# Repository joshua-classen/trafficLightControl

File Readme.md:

Traffic Light Control | Assembly

This is a school project in which I designed a traffic light circuit for the ATMega16. EAGLE files are included. The program was written in assembler.

I had uploaded this project to bitbucket years ago: https://bitbucket.org/ckrex/trafficlightcontrol/src/master/

The Code was written in Atmel AVR studio.

There is also a demo on youtube where I explain the Traffic Light Control:

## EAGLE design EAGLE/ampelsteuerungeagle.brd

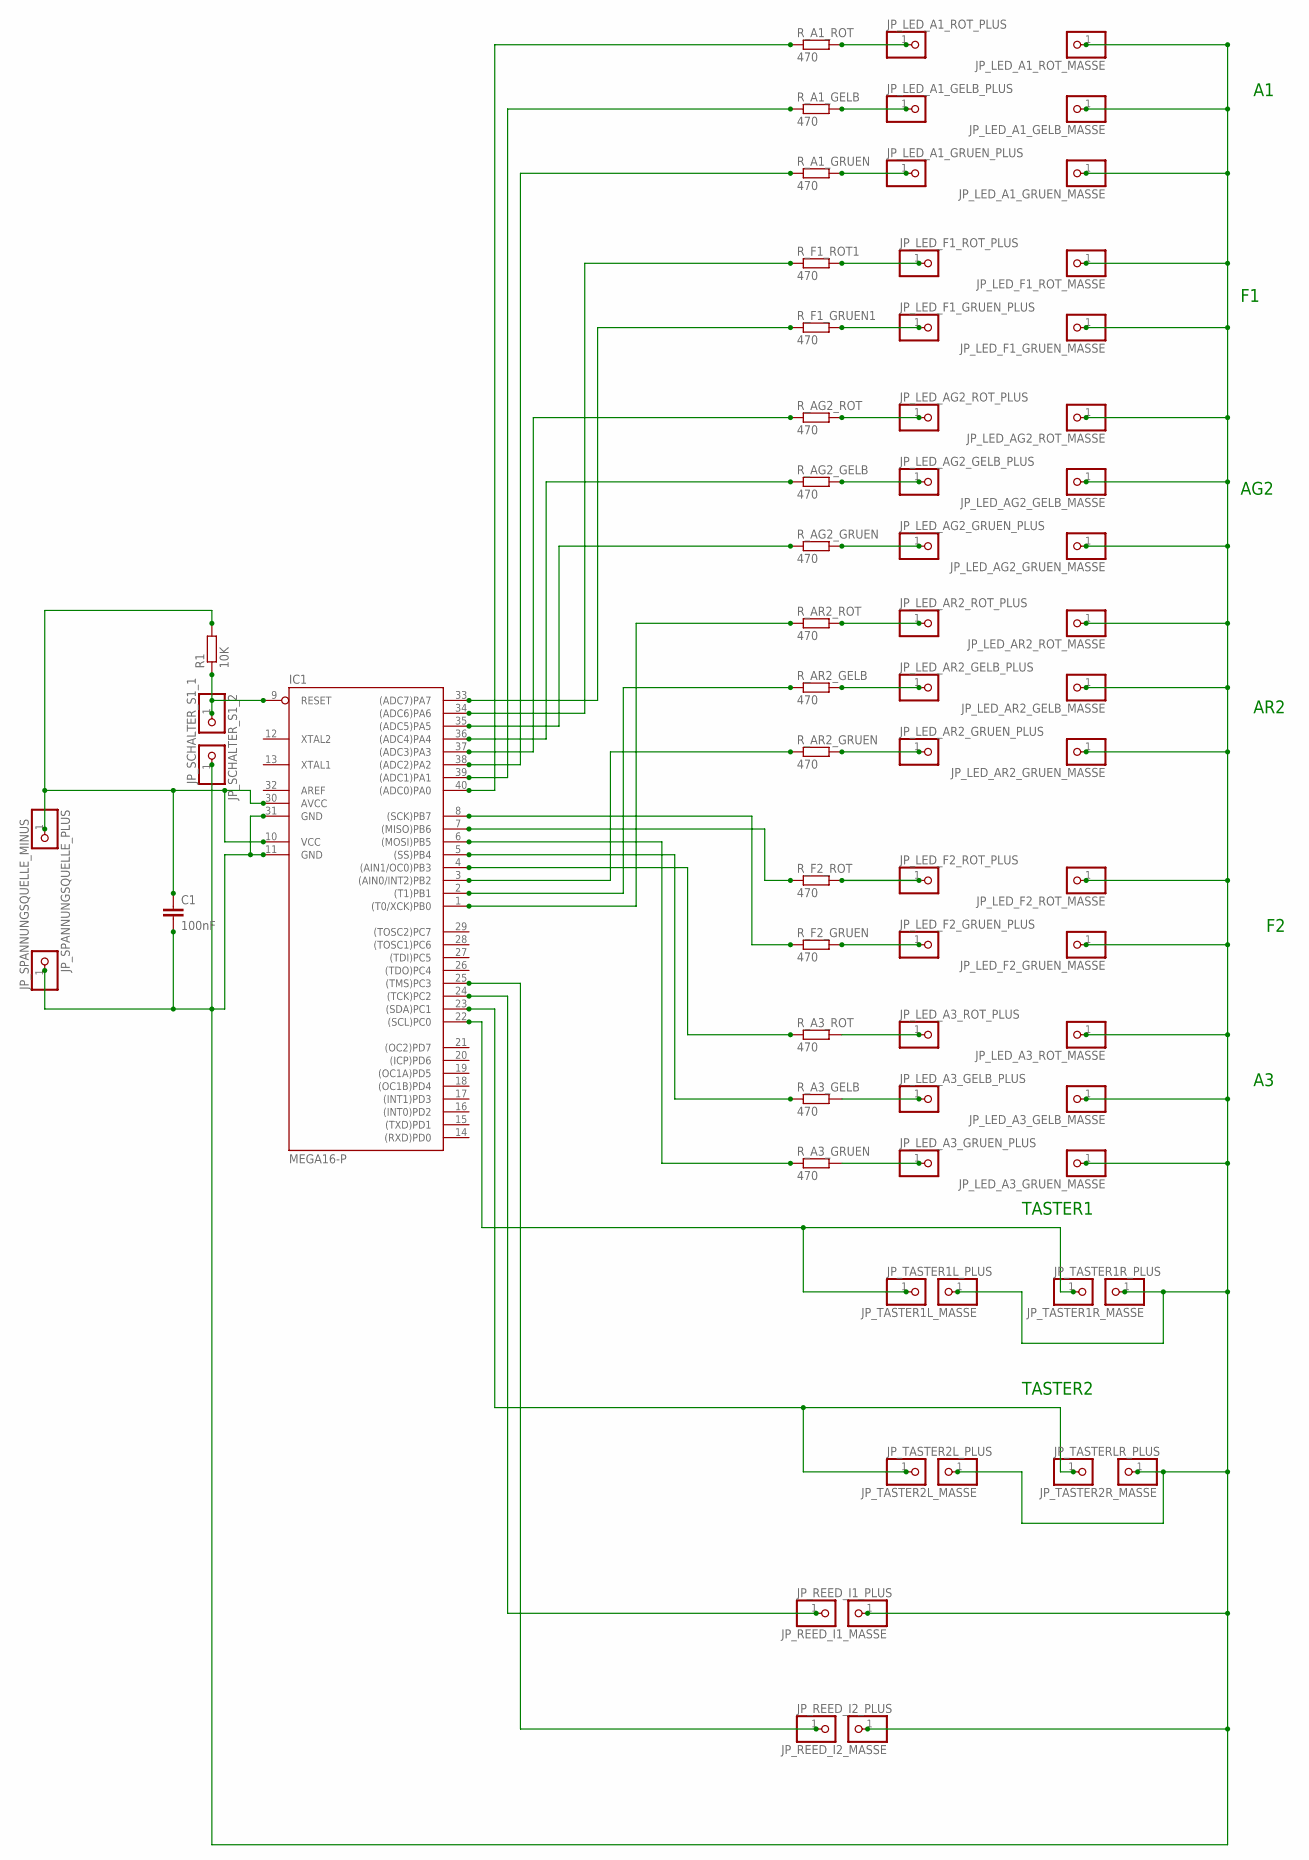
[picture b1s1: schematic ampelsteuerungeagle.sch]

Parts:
C1: 100nF; C025-024X044
IC1: MEGA16-P; DIL40
JP_LED_A1_GELB_MASSE, JP_LED_A1_GELB_PLUS, JP_LED_A1_GRUEN_MASSE, JP_LED_A1_GRUEN_PLUS, JP_LED_A1_ROT_MASSE, JP_LED_A1_ROT_PLUS, JP_LED_A3_GELB_MASSE, JP_LED_A3_GELB_PLUS, JP_LED_A3_GRUEN_MASSE, JP_LED_A3_GRUEN_PLUS, JP_LED_A3_ROT_MASSE, JP_LED_A3_ROT_PLUS: PINHD-1X1; 1X01
JP_LED_AG2_GELB_MASSE, JP_LED_AG2_GELB_PLUS, JP_LED_AG2_GRUEN_MASSE, JP_LED_AG2_GRUEN_PLUS, JP_LED_AG2_ROT_MASSE, JP_LED_AG2_ROT_PLUS: PINHD-1X1; 1X01
JP_LED_AR2_GELB_MASSE, JP_LED_AR2_GELB_PLUS, JP_LED_AR2_GRUEN_MASSE, JP_LED_AR2_GRUEN_PLUS, JP_LED_AR2_ROT_MASSE, JP_LED_AR2_ROT_PLUS: PINHD-1X1; 1X01
JP_LED_F1_GRUEN_MASSE, JP_LED_F1_GRUEN_PLUS, JP_LED_F1_ROT_MASSE, JP_LED_F1_ROT_PLUS, JP_LED_F2_GRUEN_MASSE, JP_LED_F2_GRUEN_PLUS, JP_LED_F2_ROT_MASSE, JP_LED_F2_ROT_PLUS: PINHD-1X1; 1X01
JP_REED_I1_MASSE, JP_REED_I1_PLUS, JP_REED_I2_MASSE, JP_REED_I2_PLUS: PINHD-1X1; 1X01
JP_SCHALTER_S1_1, JP_SCHALTER_S1_2: PINHD-1X1; 1X01
JP_SPANNUNGSQUELLE_MINUS: PINHD-1X1; 1X01
JP_SPANNUNGSQUELLE_PLUS: PINHD-1X1; 1X01
JP_TASTER1L_MASSE, JP_TASTER1L_PLUS, JP_TASTER1R_MASSE, JP_TASTER1R_PLUS, JP_TASTER2L_MASSE, JP_TASTER2L_PLUS, JP_TASTER2R_MASSE: PINHD-1X1; 1X01
JP_TASTERLR_PLUS: PINHD-1X1; 1X01
R1: 10K; 0204V
R_A1_GELB, R_A1_GRUEN, R_A1_ROT, R_A3_GELB, R_A3_GRUEN, R_A3_ROT: 470; 0204/7
R_AG2_GELB, R_AG2_GRUEN, R_AG2_ROT: 470; 0204/7
R_AR2_GELB, R_AR2_GRUEN, R_AR2_ROT: 470; 0204/7
R_F1_GRUEN1, R_F1_ROT1, R_F2_GRUEN, R_F2_ROT: 470; 0204/7

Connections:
unnamed: C1.1, IC1.10 (VCC), IC1.30 (AVCC), JP_SPANNUNGSQUELLE_PLUS.1, R1.2
unnamed: IC1.22 ((SCL)PC0), JP_TASTER1L_PLUS.1, JP_TASTER1R_PLUS.1
unnamed: IC1.40 ((ADC0)PA0), R_A1_ROT.1
unnamed: IC1.39 ((ADC1)PA1), R_A1_GELB.1
unnamed: IC1.38 ((ADC2)PA2), R_A1_GRUEN.1
unnamed: IC1.37 ((ADC3)PA3), R_AG2_ROT.1
unnamed: IC1.36 ((ADC4)PA4), R_AG2_GELB.1
unnamed: IC1.35 ((ADC5)PA5), R_AG2_GRUEN.1
unnamed: IC1.34 ((ADC6)PA6), R_F1_ROT1.1
unnamed: IC1.33 ((ADC7)PA7), R_F1_GRUEN1.1
unnamed: IC1.1 ((T0/XCK)PB0), R_AR2_ROT.1
unnamed: IC1.2 ((T1)PB1), R_AR2_GELB.1
unnamed: IC1.3 ((AIN0/INT2)PB2), R_AR2_GRUEN.1
unnamed: IC1.4 ((AIN1/OC0)PB3), R_A3_ROT.1
unnamed: IC1.5 ((SS)PB4), R_A3_GELB.1
unnamed: IC1.6 ((MOSI)PB5), R_A3_GRUEN.1
unnamed: IC1.7 ((MISO)PB6), R_F2_ROT.1
unnamed: JP_LED_AR2_GRUEN_PLUS.1, R_AR2_GRUEN.2
unnamed: JP_LED_A3_ROT_PLUS.1, R_A3_ROT.2
unnamed: JP_LED_AR2_GELB_PLUS.1, R_AR2_GELB.2
unnamed: JP_LED_AR2_ROT_PLUS.1, R_AR2_ROT.2
unnamed: JP_LED_AG2_GRUEN_PLUS.1, R_AG2_GRUEN.2
unnamed: JP_LED_AG2_GELB_PLUS.1, R_AG2_GELB.2
unnamed: JP_LED_AG2_ROT_PLUS.1, R_AG2_ROT.2
unnamed: JP_LED_A1_GRUEN_PLUS.1, R_A1_GRUEN.2
unnamed: JP_LED_A1_GELB_PLUS.1, R_A1_GELB.2
unnamed: JP_LED_A1_ROT_PLUS.1, R_A1_ROT.2
unnamed: JP_LED_F1_ROT_PLUS.1, R_F1_ROT1.2
unnamed: JP_LED_F1_GRUEN_PLUS.1, R_F1_GRUEN1.2
unnamed: JP_LED_F2_ROT_PLUS.1, R_F2_ROT.2
unnamed: JP_LED_F2_GRUEN_PLUS.1, R_F2_GRUEN.2
unnamed: JP_LED_A3_GELB_PLUS.1, R_A3_GELB.2
unnamed: JP_LED_A3_GRUEN_PLUS.1, R_A3_GRUEN.2
unnamed: IC1.9 (RESET), JP_SCHALTER_S1_2.1, R1.1
unnamed: IC1.23 ((SDA)PC1), JP_TASTER2L_PLUS.1, JP_TASTERLR_PLUS.1
unnamed: IC1.24 ((TCK)PC2), JP_REED_I1_PLUS.1
unnamed: C1.2, IC1.11 (GND), IC1.31 (GND), JP_LED_A1_GELB_MASSE.1, JP_LED_A1_GRUEN_MASSE.1, JP_LED_A1_ROT_MASSE.1, JP_LED_A3_GELB_MASSE.1, JP_LED_A3_GRUEN_MASSE.1, JP_LED_A3_ROT_MASSE.1, JP_LED_AG2_GELB_MASSE.1, JP_LED_AG2_GRUEN_MASSE.1, JP_LED_AG2_ROT_MASSE.1, JP_LED_AR2_GELB_MASSE.1, JP_LED_AR2_GRUEN_MASSE.1, JP_LED_AR2_ROT_MASSE.1, JP_LED_F1_GRUEN_MASSE.1, JP_LED_F1_ROT_MASSE.1, JP_LED_F2_GRUEN_MASSE.1, JP_LED_F2_ROT_MASSE.1, JP_REED_I1_MASSE.1, JP_REED_I2_MASSE.1, JP_SCHALTER_S1_1.1, JP_SPANNUNGSQUELLE_MINUS.1, JP_TASTER1L_MASSE.1, JP_TASTER1R_MASSE.1, JP_TASTER2L_MASSE.1, JP_TASTER2R_MASSE.1
unnamed: IC1.25 ((TMS)PC3), JP_REED_I2_PLUS.1
unnamed: IC1.8 ((SCK)PB7), R_F2_GRUEN.1

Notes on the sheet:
AG2
AR2
TASTER1
TASTER2

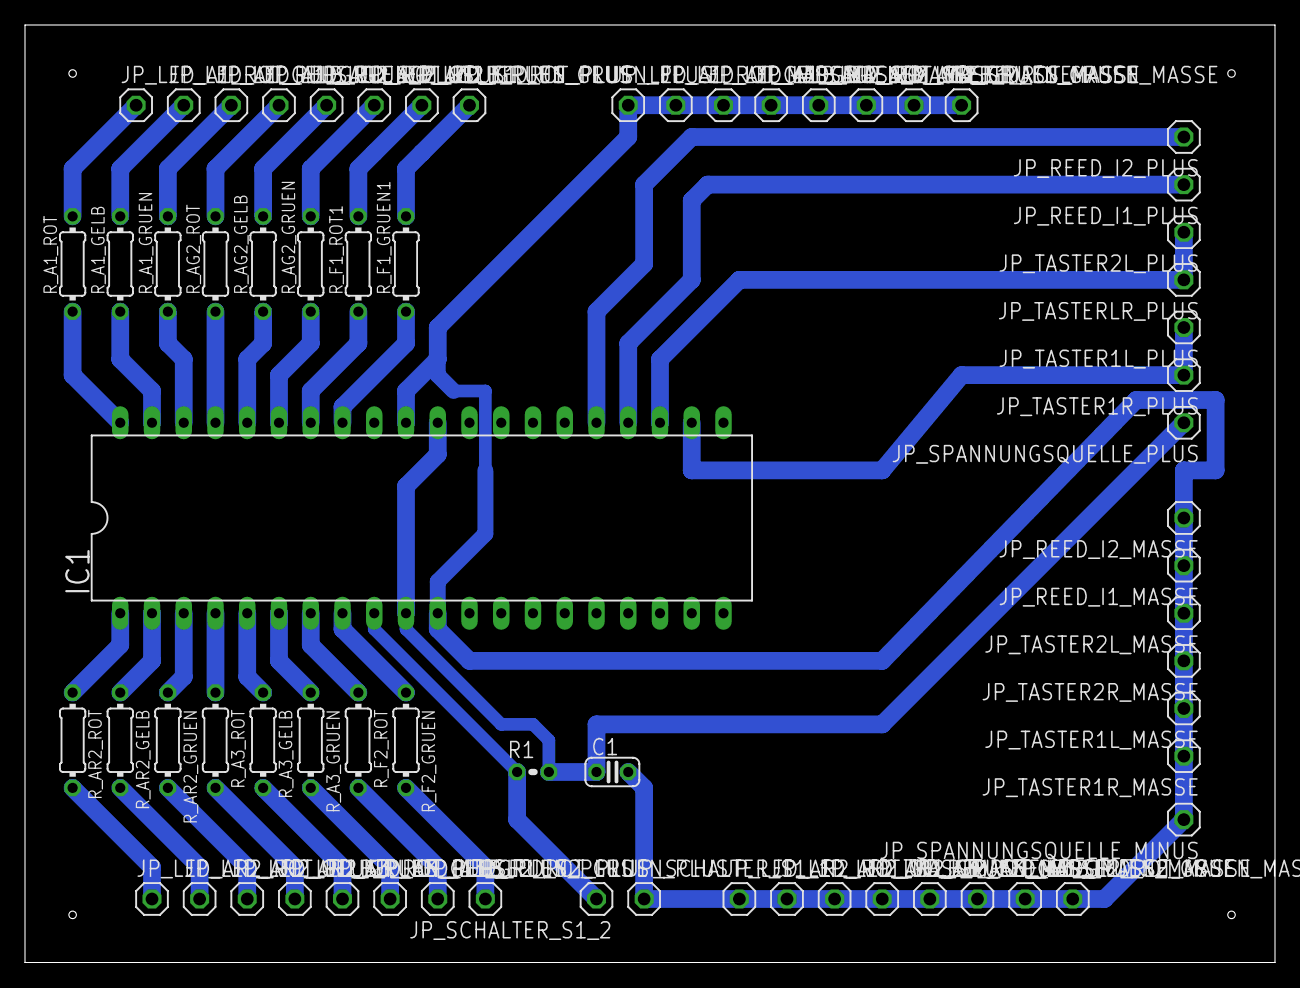
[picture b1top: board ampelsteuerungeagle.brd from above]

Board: 2 copper layers, 100.0 x 75.0 mm, 67 parts (0 on the bottom side), 39 nets.

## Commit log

2022-11-16 Added all code and EAGLE Files to repo;
2022-11-17 added youtube image to Readme
